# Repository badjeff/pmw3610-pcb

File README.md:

# PMW3610 PCB

[PixArt PMW3610DM-SUDU](https://www.pixart.com/products-detail/21/PMW3610DM-SUDU) low power laser mouse sensor breakout board.

- Base on schematic from [siderakb/pmw3610-pcb](https://github.com/siderakb/pmw3610-pcb).
- Be operated with 3.3V voltage level ONLY.
- Outlined as narrow as possible for side mount horizontally and perpendicular on low profile keyboards.
- Developed for [zmk-pmw3610-driver](https://github.com/badjeff/zmk-pmw3610-driver)

*Figure 1: Size comparing to Seeed XIAO BLE*

## PCB

Online preview avaliable [here](https://kicanvas.org/?github=https%3A%2F%2Fgithub.com%2Fbadjeff%2Fpmw3610-pcb), powered by [KiCanvas](https://github.com/theacodes/kicanvas).

*Figure 2: PCB edgecuts dimension*

### BOM

|Ref|Value|Footprint|
|-|-|-|
|C1|3.3uF/16V|SMD 0603|
|C2, C3|100nF|SMD 0603|
|C4|100nF X7R|SMD 0603|
|C5|10nF|SMD 0603|
|C6|10uF X7R|SMD 0603|
|C7|10nF X7R|SMD 0603|
|C8, C9|1uF|SMD 0603|
|C10| DNI |SMD 0603|
|R1|10k|SMD 0603|
|U1|PMW3610|16 Pin|
|U2|TLV74318|SOT-23-5|
|J1, J2|2.54mm Pin header||
- DNI: don't install.
- SMD 0603 (Imperial) aka 1608 Metric.
- PMW3610 needs to be used with LM18-LSI lens.
- `R1` is optional/additional RESET pull up resistor, RESET pin of PMW3610 has a built in weak pull up circuit.
- `U2` LDO can be replace by RT9193-18GB, change `C10` to 22nF.
- Solder extra decoupling capacitors (C4, C6, C7) directly to the pins of the sensor, if needed.

### Board Characteristics

- Copper layer count: 2
- Board thickness: 1.6 mm
- Board overall dimensions: 15.5 x 30 mm

### Voltage level config

- 3.3V logic
- VIN: 3.3V

## License

Available under the [CERN-OHL-P v2](/LICENSE) permissive license.

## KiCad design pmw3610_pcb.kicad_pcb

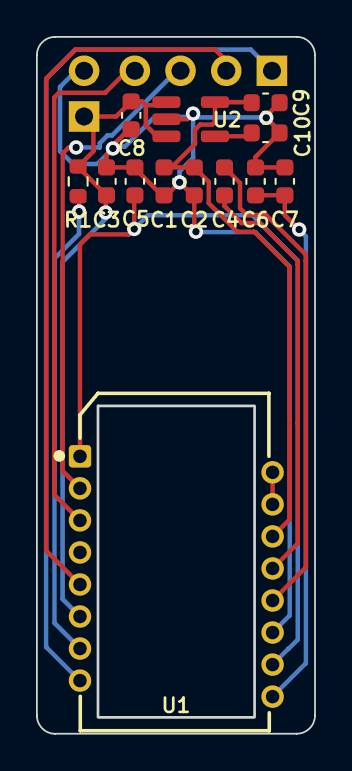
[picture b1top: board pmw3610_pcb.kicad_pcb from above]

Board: 2 copper layers, 15.5 x 38.7 mm, 15 parts (0 on the bottom side), 14 nets.

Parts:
C1: 3.3uF/16V; C_0603_1608Metric
C2, C3: 100nF; C_0603_1608Metric
C4: 100nF X7R; C_0603_1608Metric
C5: 10nF; C_0603_1608Metric
C6: 10uF X7R; C_0603_1608Metric
C7: 10nF X7R; C_0603_1608Metric
C8, C9: 1uF; C_0603_1608Metric
C10: 22nF; C_0603_1608Metric
J1: Conn_01x02; PinHeader_1x02_P2.54mm_Vertical
J2: Conn_01x04; PinHeader_1x04_P2.54mm_Vertical
R1: 10k; R_0603_1608Metric
U1: PMW3610; PMW3610DM-SUDU 16Pin
U2: TLV74318PDBVR; SOT-23-5_HandSoldering

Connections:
+1V8: C1.1, C2.1, C9.1, U1.14 (VDD), U2.5 (OUT)
GND: C1.2, C2.2, C3.2, C5.2, C6.2, C7.2, C8.2, C9.2, C10.2, J1.2, U1.11 (GND), U2.2 (GND)
MOTION: J2.1, U1.8 (MOTION)
unnamed: C5.1, U1.1 (+VCSEL), U1.10 (PASS_T)
unnamed: U1.15 (XYLASER), U1.16 (-VCSEL)
unnamed: C4.2, U1.13 (CN)
unnamed: C4.1, U1.12 (CP)
unnamed: R1.2, U1.7 (NRESET)
unnamed: C6.1, C7.1, U1.9 (VCP)
unnamed: C10.1, U2.4 (NC)
SCLK: J2.4, U1.3 (SCLK)
SDIO: J2.3, U1.2 (SDIO)
VIN: C3.1, C8.1, J1.1, R1.1, U1.6 (VDDIO), U2.1 (IN), U2.3 (EN)
nCS: J2.2, U1.5 (NCS)

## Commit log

2025-04-13 variant of long flex pcb

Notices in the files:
pmw3610_pcb.kicad_pcb:
Open Source Hardware, CERN-OHL-P v2
